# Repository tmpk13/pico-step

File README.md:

# pico-step

Closed-loop stepper driver board: RP2354A + TMC5241 motion controller and
driver (integrated 65 V bridges) + TLE5012B magnetic angle sensor.
USB-C powered logic, separate motor supply (VM) up to 48 V.

The schematic is drawn as text in `tsch/` for the text-schematic tool
`tsch` (set `TSCH` to its binary when it is not on the PATH); `mise run sch`
builds it into `pico-step.kicad_sch`, which is generated and not committed.

```sh
mise run install   # test deps
mise run sch-check # check the tsch/ drawing (fast, no KiCad)
mise run sch       # tsch/ -> pico-step.kicad_sch + sheets, proven with kicad-cli
mise run erc
mise run test
mise run render    # build/tsch/pico-step-<sheet>.png
mise run pcb-sync  # board <- schematic (footprints, values, nets), keeps placement
mise run pcb-place # placement table -> board (overwrites GUI moves)
mise run pcb-dsn   # build/pico-step.dsn for freerouting
mise run pcb-autoroute # FREEROUTING=<launcher or jar> freerouting -> build/pico-step.ses
mise run pcb-ses   # import the session and refill zones
mise run pcb-gnd   # GND stitching vias after routing
mise run pcb-drc
mise run pcb-render # build/pcb-top.png, build/pcb-bottom.png
```

The PCB is a 42 mm NEMA17 back-mount, 2 layers, 0.15 mm rules; the floor
plan is in `notes/pcb.md`.

See `ARCHITECTURE.md` for the block diagram, `BOM.md` for sourced parts,
`PARTS_BY_CHIP.md` for which parts support which chip,
`DIGIKEY.md` for the order list,
`TODO.md` for open work.

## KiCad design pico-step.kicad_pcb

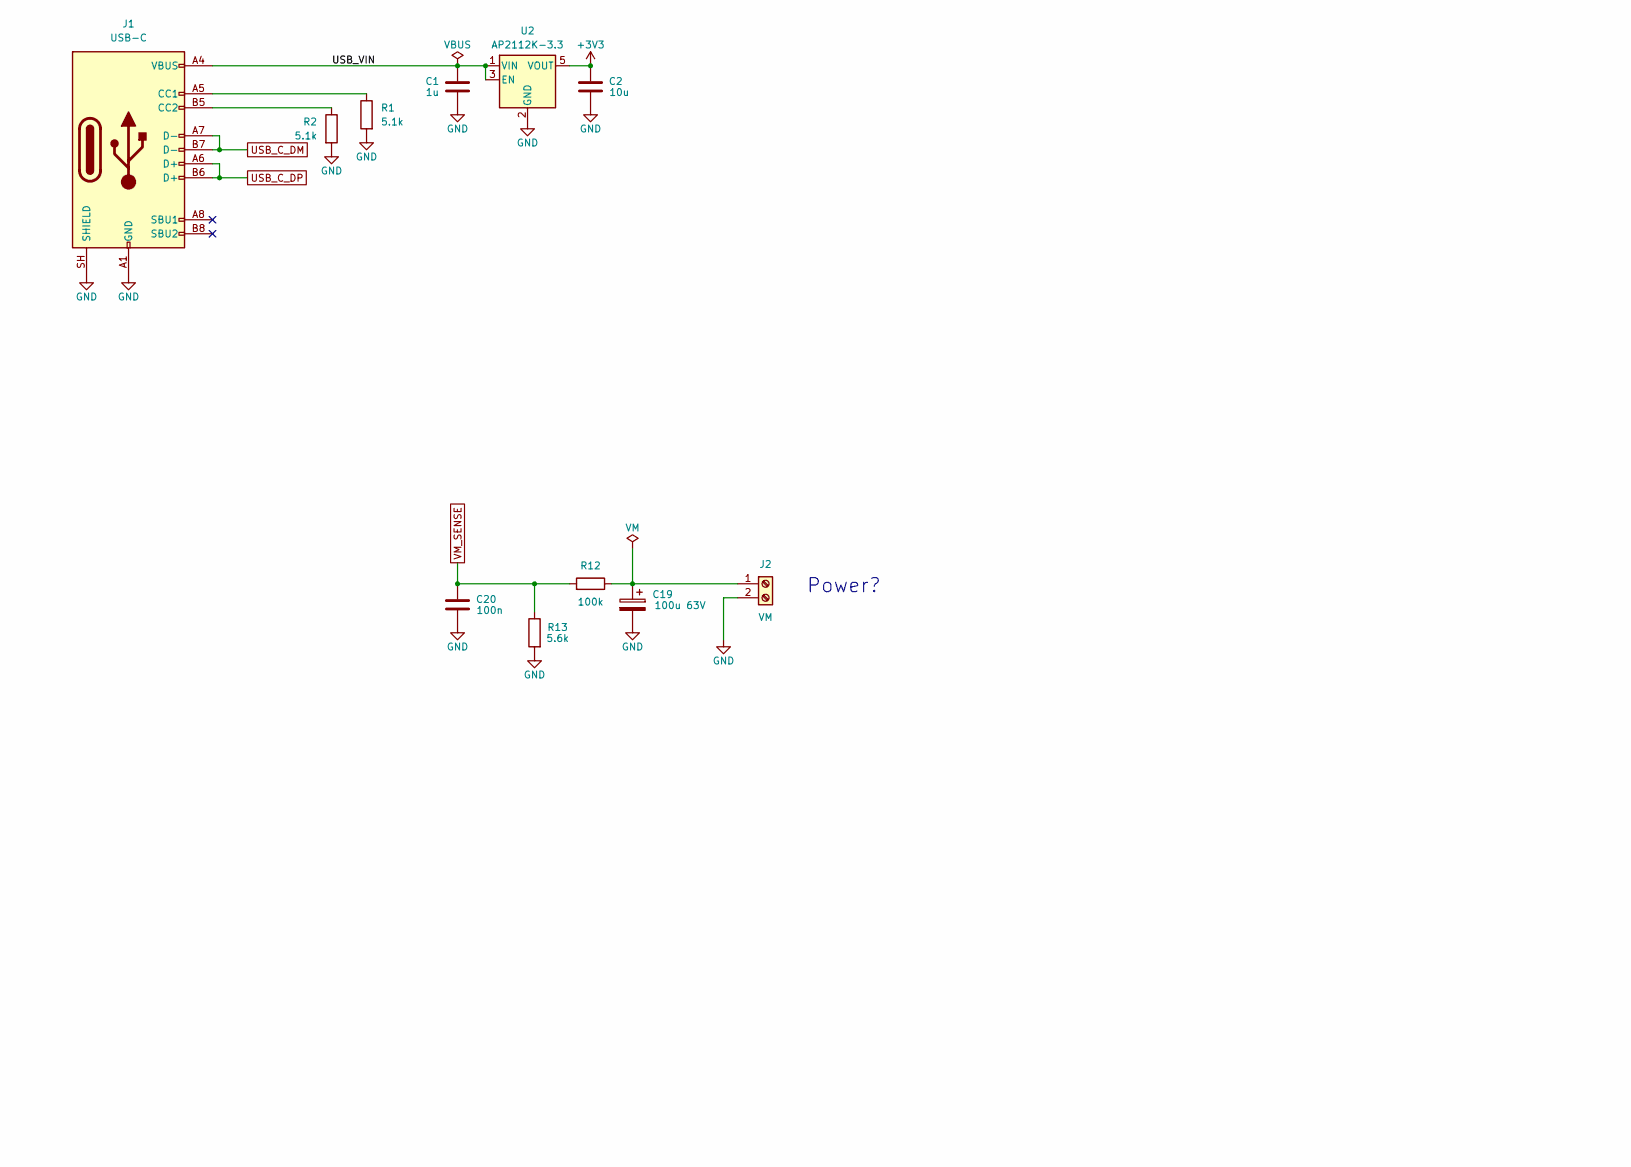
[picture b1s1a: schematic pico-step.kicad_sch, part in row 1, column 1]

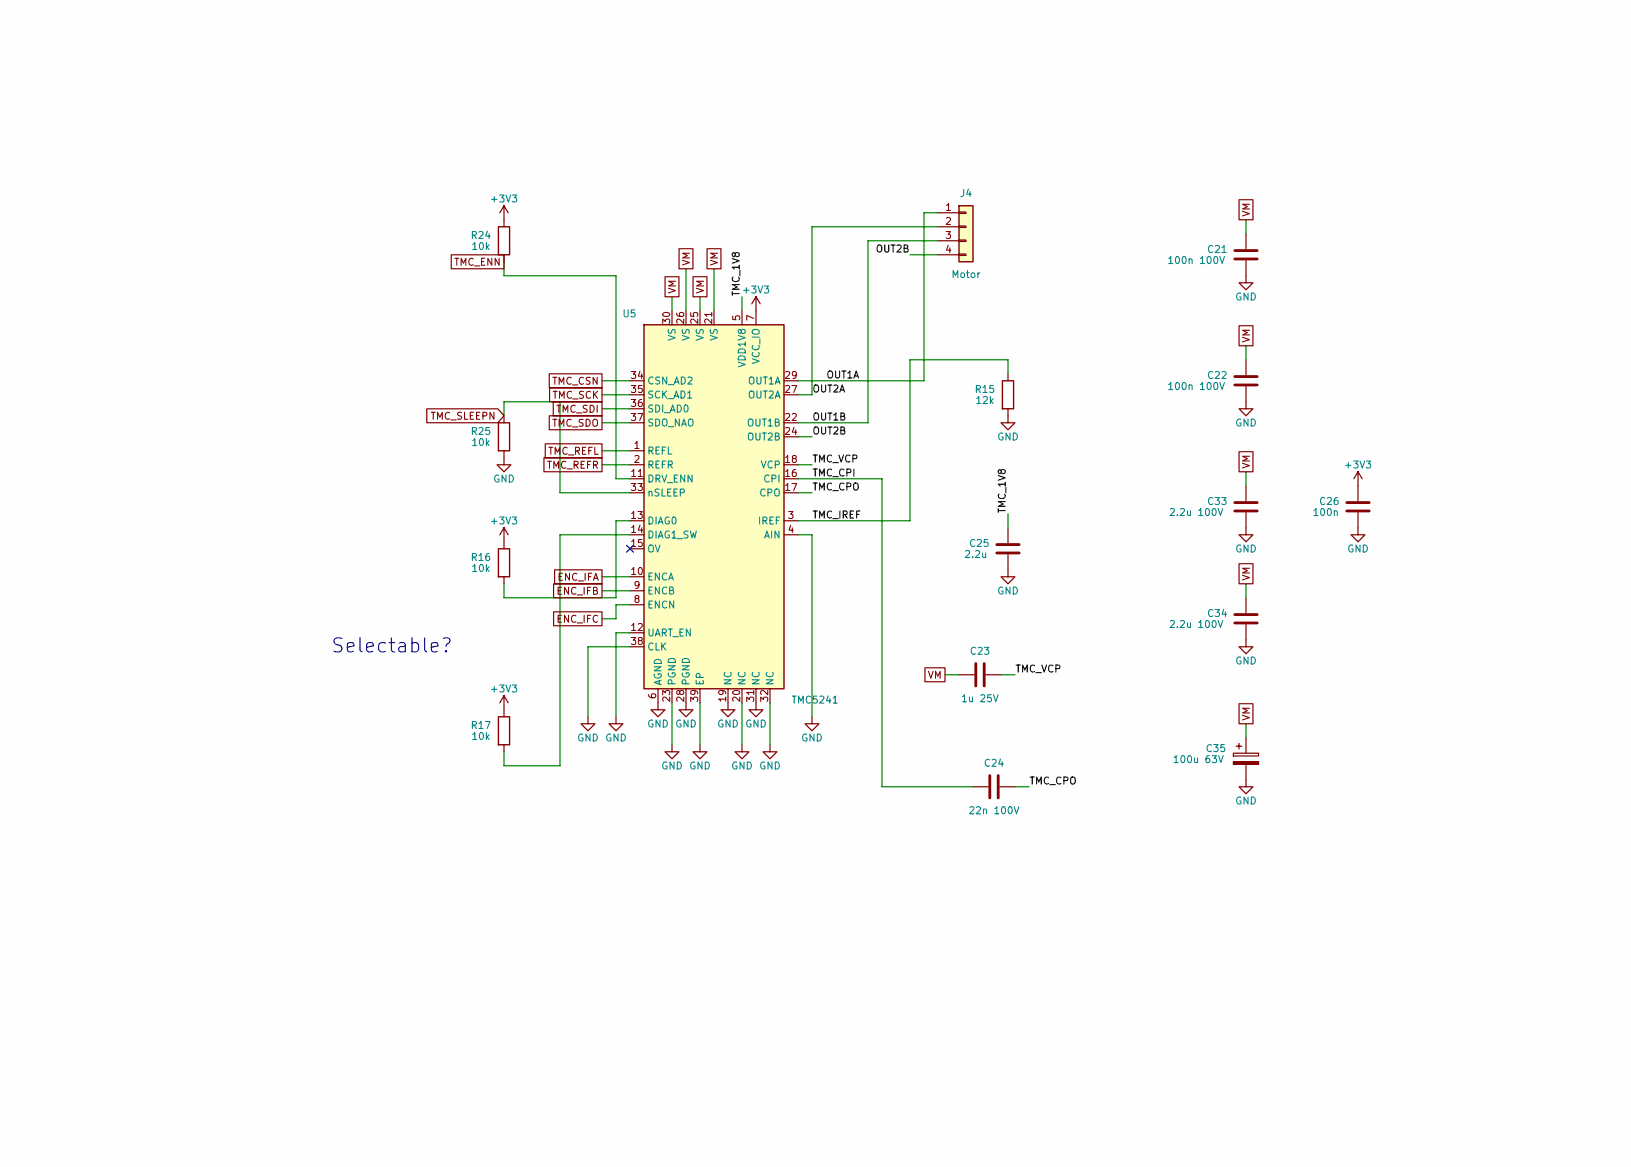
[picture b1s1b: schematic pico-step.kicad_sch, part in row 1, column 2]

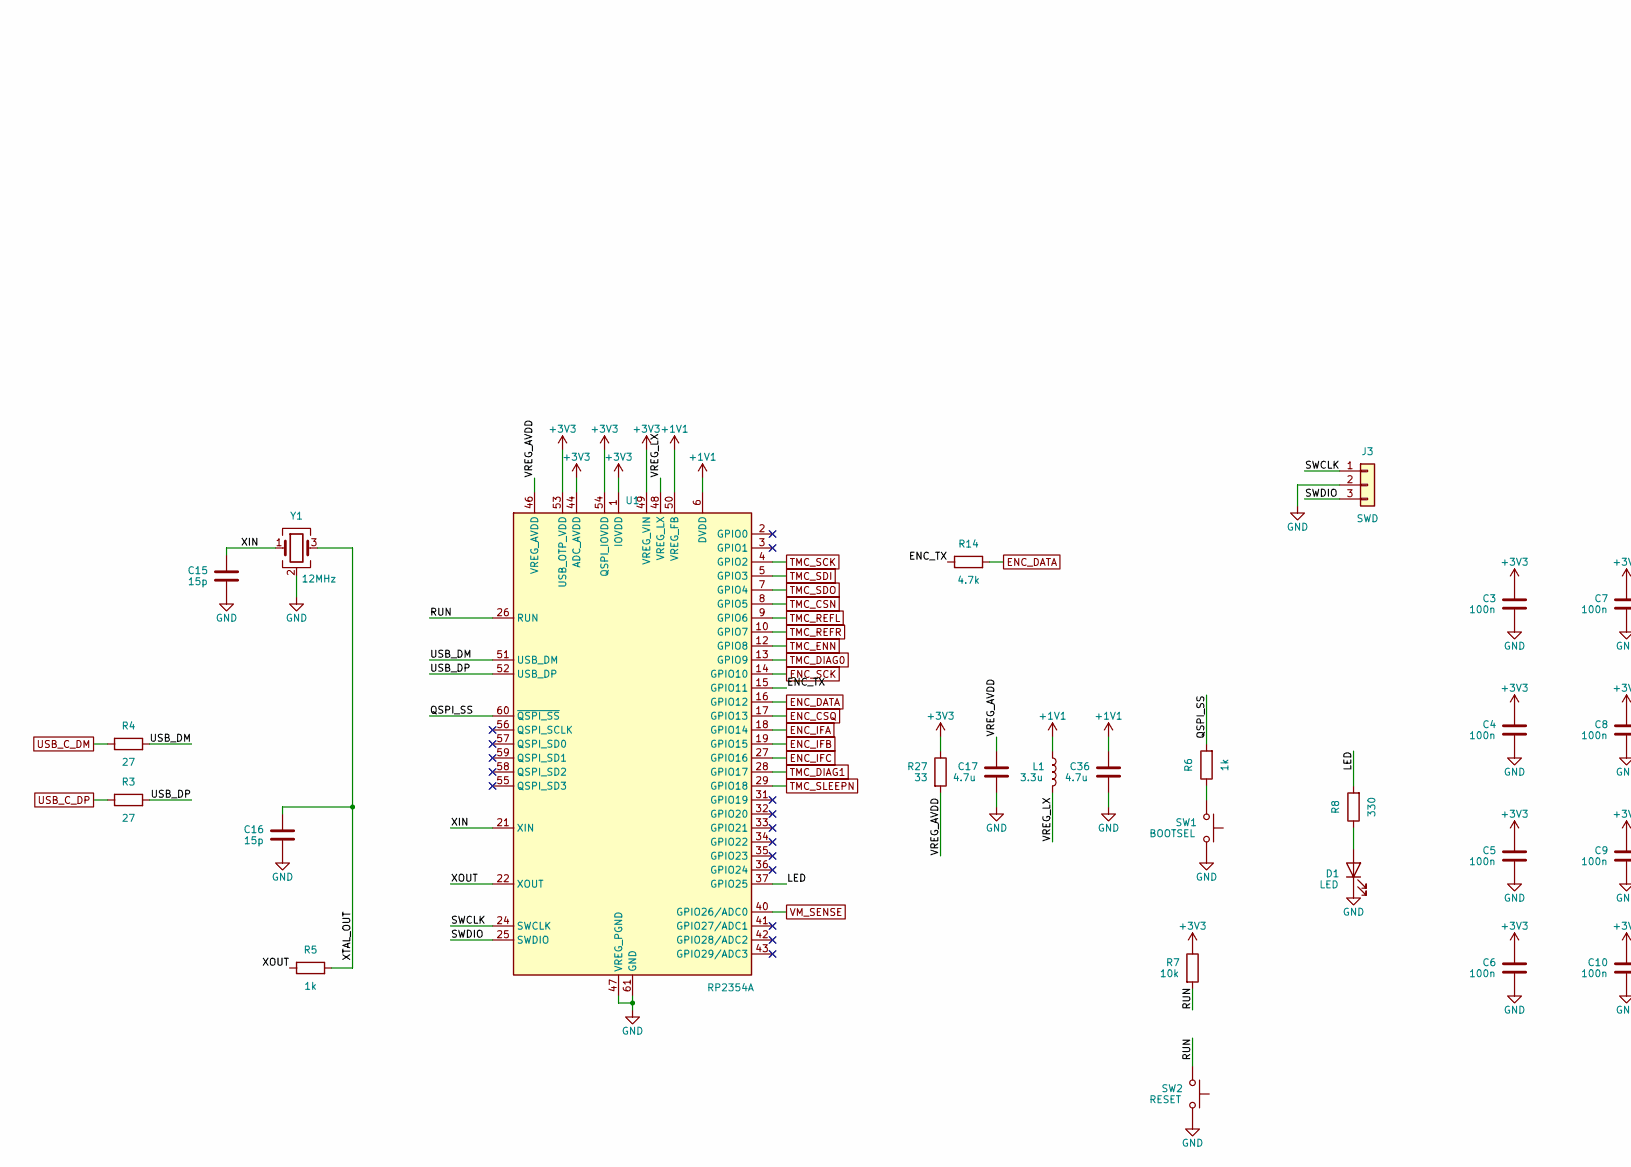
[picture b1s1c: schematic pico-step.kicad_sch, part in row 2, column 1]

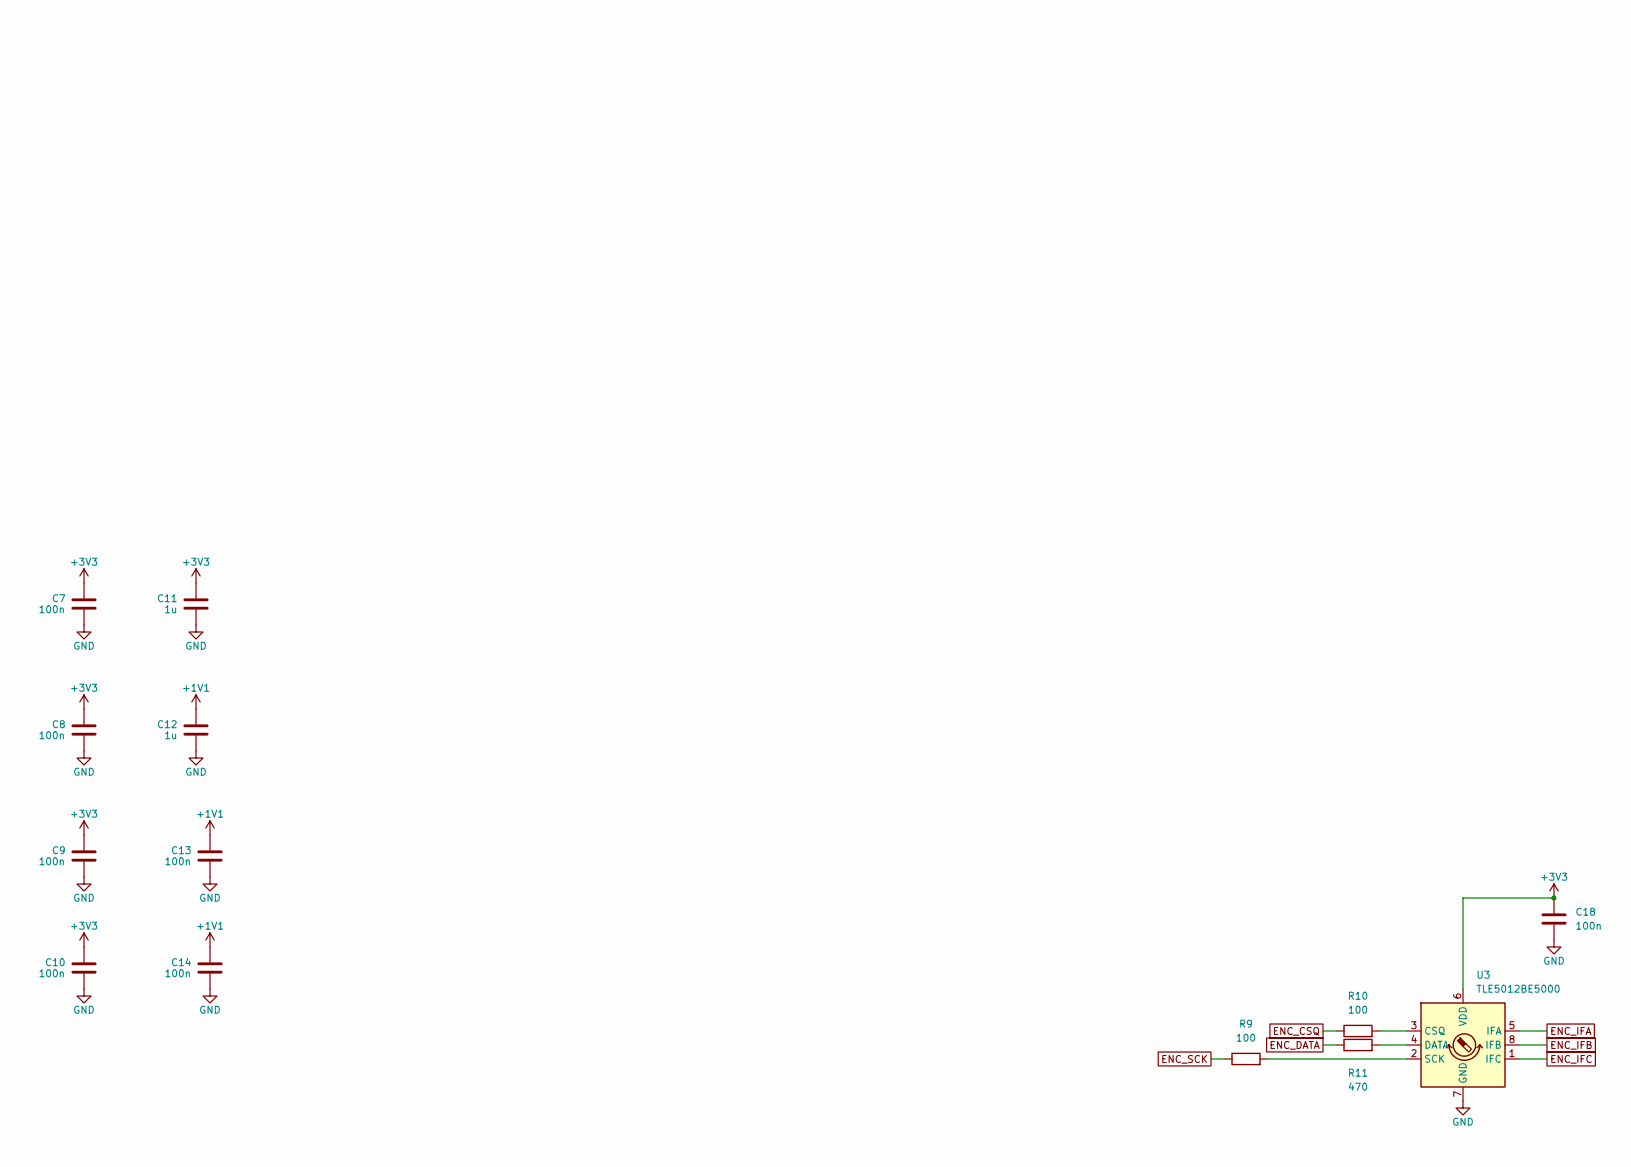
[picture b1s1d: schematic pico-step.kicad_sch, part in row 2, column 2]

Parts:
C1, C11, C12: 1u; C_0603_1608Metric
C2: 10u; C_0805_2012Metric
C3, C4, C5, C6, C7, C8, C9, C10, C13, C14, C18, C20, C26: 100n; C_0603_1608Metric
C15, C16: 15p; C_0603_1608Metric
C17, C36: 4.7u; C_0603_1608Metric
C19, C35: 100u 63V; CP_Elec_10x10.5
C21, C22: 100n 100V; C_0603_1608Metric
C23: 1u 25V; C_0603_1608Metric
C24: 22n 100V; C_0603_1608Metric
C25: 2.2u; C_0603_1608Metric
C33, C34: 2.2u 100V; C_1210_3225Metric
D1: LED; LED_0603_1608Metric
J1: USB-C; USB_C_Receptacle_GCT_USB4105-xx-A_16P_SH; MPN USB4105-GF-A
J2: VM; TerminalBlock_Phoenix_MKDS-1,5-2-5.08_1x02_P5.08mm_Horizont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
J3: SWD; PinHeader_1x03_P2.54mm_Vertical
J4: Motor; JST_XH_B4B-XH-A_1x04_P2.50mm_Vertical
L1: 3.3u; L_Abracon_AOTA-B201610; MPN AOTA-B201610S3R3-101-T
R1, R2: 5.1k; R_0603_1608Metric
R3, R4: 27; R_0603_1608Metric
R5, R6: 1k; R_0603_1608Metric
R7, R16, R17, R24, R25: 10k; R_0603_1608Metric
R8: 330; R_0603_1608Metric
R9, R10: 100; R_0603_1608Metric
R11: 470; R_0603_1608Metric
R12: 100k; R_0603_1608Metric
R13: 5.6k; R_0603_1608Metric
R14: 4.7k; R_0603_1608Metric
R15: 12k; R_0603_1608Metric
R27: 33; R_0603_1608Metric
SW1: BOOTSEL; SW_SPST_PTS810
SW2: RESET; SW_SPST_PTS810
U1: RP2354A; QFN-60-1EP_7x7mm_P0.4mm_EP3.4x3.4mm; MPN SC1511-A4
U2: AP2112K-3.3; SOT-23-5; MPN AP2112K-3.3TRG1
U3: TLE5012BE5000; Infineon_PG-DSO-8; MPN TLE5012BE5000XUMA1
U5: TMC5241; ADI_TQFN-38-1EP_5x7mm_P0.5mm_EP3.65x5.6mm_ThermalVias; MPN TMC5241ATU+T
Y1: 12MHz; Crystal_SMD_3225-4Pin_3.2x2.5mm; MPN ABM8-272-T3

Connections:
+1V1: C12.1, C13.1, C14.1, C36.1, L1.1, U1.6 (DVDD), U1.23 (DVDD), U1.39 (DVDD), U1.50 (VREG_FB)
+3V3: C2.1, C3.1, C4.1, C5.1, C6.1, C7.1, C8.1, C9.1, C10.1, C11.1, C18.1, C26.1, R7.1, R16.1, R17.1, R24.1, R27.1, U1.1 (IOVDD), U1.11 (IOVDD), U1.20 (IOVDD), U1.30 (IOVDD), U1.38 (IOVDD), U1.44 (ADC_AVDD), U1.45 (IOVDD), U1.49 (VREG_VIN), U1.53 (USB_OTP_VDD), U1.54 (QSPI_IOVDD), U2.5 (VOUT), U3.6 (VDD), U5.7 (VCC_IO)
/driver/OUT1A: J4.1, U5.29 (OUT1A)
/driver/OUT1B: J4.3, U5.22 (OUT1B)
/driver/OUT2A: J4.2, U5.27 (OUT2A)
/driver/OUT2B: J4.4, U5.24 (OUT2B)
ENC_CSQ: R10.1, U1.17 (GPIO13)
ENC_DATA: R11.1, R14.2, U1.16 (GPIO12)
ENC_IFA: U1.18 (GPIO14), U3.5 (IFA), U5.10 (ENCA)
ENC_IFB: U1.19 (GPIO15), U3.8 (IFB), U5.9 (ENCB)
ENC_IFC: U1.27 (GPIO16), U3.1 (IFC), U5.8 (ENCN)
ENC_SCK: R9.1, U1.14 (GPIO10)
ENC_TX: R14.1, U1.15 (GPIO11)
GND: C1.2, C2.2, C3.2, C4.2, C5.2, C6.2, C7.2, C8.2, C9.2, C10.2, C11.2, C12.2, C13.2, C14.2, C15.2, C16.2, C17.2, C18.2, C19.2, C20.2, C21.2, C22.2, C25.2, C26.2, C33.2, C34.2, C35.2, C36.2, D1.1 (K), J1.A1 (GND), J1.A12 (GND), J1.B1 (GND), J1.B12 (GND), J1.SH (SHIELD), J2.2, J3.2, R1.2, R2.2, R13.2, R15.2, R25.2, SW1.2, SW2.2, U1.47 (VREG_PGND), U1.61 (GND), U2.2 (GND), U3.7 (GND), U5.4 (AIN), U5.6 (AGND), U5.12 (UART_EN), U5.19 (NC), U5.20 (NC), U5.23 (PGND), U5.28 (PGND), U5.31 (NC), U5.32 (NC), U5.38 (CLK), U5.39 (EP), Y1.2 (G), Y1.4 (G)
unnamed: C16.1, R5.2, Y1.3
unnamed: D1.2 (A), R8.1
unnamed: J1.A5 (CC1), R1.1
unnamed: J1.B5 (CC2), R2.1
unnamed: J1.A6 (D+), J1.B6 (D+), R3.1
unnamed: J1.A7 (D-), J1.B7 (D-), R4.1
unnamed: J3.1, U1.24 (SWCLK)
unnamed: J3.3, U1.25 (SWDIO)
unnamed: R6.1, SW1.1
unnamed: C17.1, R27.2, U1.46 (VREG_AVDD)
unnamed: L1.2, U1.48 (VREG_LX)
unnamed: R8.2, U1.37 (GPIO25)
unnamed: R6.2, U1.60 (~QSPI_SS)
unnamed: R7.2, SW2.1, U1.26 (RUN)
unnamed: C15.1, U1.21 (XIN), Y1.1
unnamed: R5.1, U1.22 (XOUT)
unnamed: C1.1, J1.A4 (VBUS), J1.A9 (VBUS), J1.B4 (VBUS), J1.B9 (VBUS), U2.1 (VIN), U2.3 (EN)
unnamed: R10.2, U3.3 (CSQ)
unnamed: R11.2, U3.4 (DATA)
unnamed: R9.2, U3.2 (SCK)
unnamed: C24.1, U5.16 (CPI)
unnamed: C24.2, U5.17 (CPO)
unnamed: R16.2, U5.13 (DIAG0)
unnamed: R17.2, U5.14 (DIAG1_SW)
unnamed: R15.1, U5.3 (IREF)
unnamed: C23.2, U5.18 (VCP)
unnamed: C25.1, U5.5 (VDD1V8)
TMC_CSN: U1.8 (GPIO5), U5.34 (CSN_AD2)
TMC_DIAG0: U1.13 (GPIO9)
TMC_DIAG1: U1.28 (GPIO17)
TMC_ENN: R24.2, U1.12 (GPIO8), U5.11 (DRV_ENN)
TMC_REFL: U1.9 (GPIO6), U5.1 (REFL)
TMC_REFR: U1.10 (GPIO7), U5.2 (REFR)
TMC_SCK: U1.4 (GPIO2), U5.35 (SCK_AD1)
TMC_SDI: U1.5 (GPIO3), U5.36 (SDI_AD0)
TMC_SDO: U1.7 (GPIO4), U5.37 (SDO_NAO)
TMC_SLEEPN: R25.1, U1.29 (GPIO18), U5.33 (nSLEEP)
USB_DM: R4.2, U1.51 (USB_DM)
USB_DP: R3.2, U1.52 (USB_DP)
VM: C21.1, C22.1, C23.1, C33.1, C34.1, C35.1, U5.21 (VS), U5.25 (VS), U5.26 (VS), U5.30 (VS)
VM_IN: C19.1, J2.1, R12.1
VM_SENSE: C20.1, R12.2, R13.1, U1.40 (GPIO26/ADC0)

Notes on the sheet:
Selectable?
Power?

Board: 4 copper layers, 63 parts (14 on the bottom side), 54 nets, no tracks yet.

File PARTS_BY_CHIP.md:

# Parts by chip

Every one of the 63 parts on the board, grouped by the chip it supports.

## U1 RP2354A

| Function | Parts |
| --- | --- |
| Decoupling, IOVDD | C3..C8 100n |
| Decoupling, USB_OTP_VDD + QSPI_IOVDD / ADC_AVDD | C9 100n, C10 100n |
| Core regulator, CIN / COUT / inductor | C11 4.7u, C12 4.7u, L1 3.3u |
| Core regulator, VREG_AVDD filter | R27 33, C17 4.7u |
| Decoupling, DVDD (pins 6, 39, 23) | C13 100n, C14 100n, C36 4.7u |
| 12 MHz crystal | Y1, C15 15p, C16 15p, R5 1k (XOUT) |
| USB series resistors | R3 27, R4 27 |
| BOOTSEL and reset | R6 1k, SW1 BOOTSEL, R7 10k, SW2 RESET |
| SWD header | J3 |
| Status LED (GPIO25) | R8 330, D1 |

## U5 TMC5241

| Function | Parts |
| --- | --- |
| VS decoupling, pin 30 end / pin 21 end of the VS/OUT row | C21 100n 100V, C33 2.2u 100V / C22 100n 100V, C34 2.2u 100V |
| VS bulk | C35 100u 63V |
| Charge pump | C23 1u 25V (VCP-VS), C24 22n 100V (CPI-CPO) |
| VDD1V8 regulator | C25 2.2u |
| VCC_IO | C26 100n |
| Full-scale current (RREF) | R15 12k |
| DIAG0/DIAG1 pull-ups | R16 10k, R17 10k |
| DRV_ENN pull-up (off during MCU reset) | R24 10k |
| nSLEEP pull-down (asleep until firmware wakes it) | R25 10k |
| Motor connector | J4 |

## U3 TLE5012B

| Function | Parts |
| --- | --- |
| Decoupling | C18 100n |
| SSC series resistors | R9 100 (SCK), R10 100 (CSQ), R11 470 (DATA) |
| SPI1 TX into DATA (TX cannot tri-state) | R14 4.7k |

## U2 AP2112K-3.3

| Function | Parts |
| --- | --- |
| Input / output caps | C1 1u, C2 10u |

## Not tied to one chip

| Function | Parts |
| --- | --- |
| USB-C input, CC pull-downs | J1, R1 5.1k, R2 5.1k |
| Motor supply terminal and bulk (feeds U5) | J2, C19 100u 63V |
| VM_SENSE divider (feeds U1 GPIO26 ADC0) | R12 100k, R13 5.6k, C20 100n |

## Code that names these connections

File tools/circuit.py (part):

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connect("GND", "J3.2")
connect("SWDIO", "U1.25", "J3.3")

# Status LED on GPIO25
res("R8", "330")
part("D1", "Device:LED", "LED", "LED_SMD:LED_0603_1608Metric")
connect("LED", "U1.37", "R8.1")
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res("R14", "4.7k")
connect("+3V3", "U3.6", "C18.1")
connect("GND", "U3.7", "C18.2")
connect("ENC_SCK", "U1.14", "R9.1")       # GPIO10 SPI1 SCK
connect("ENC_SCK_S", "R9.2", "U3.2")
connect("ENC_CSQ", "U1.17", "R10.1")      # GPIO13 SPI1 CSn
connect("ENC_CSQ_S", "R10.2", "U3.3")
connect("ENC_TX", "U1.15", "R14.1")       # GPIO11 SPI1 TX
connect("ENC_DATA", "U1.16", "R14.2", "R11.1")  # GPIO12 SPI1 RX
connect("ENC_DATA_S", "R11.2", "U3.4")
connect("ENC_IFA", "U1.18", "U3.5")       # GPIO14, PWM output in E5000
connect("ENC_IFB", "U1.19", "U3.8")       # GPIO15
connect("ENC_IFC", "U1.27", "U3.1")       # GPIO16

groups.append({"name": "encoder", "stages": [
    ["R9", "R10", "R14", "R11"], ["U3", "C18"],
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cap("C20", "100n")
connect("VM", "J2.1", "C19.1", "R12.1")
connect("GND", "J2.2", "C19.2", "R13.2", "C20.2")
connect("VM_SENSE", "R12.2", "R13.1", "C20.1", "U1.40")  # GPIO26 ADC0

groups.append({"name": "motor_supply", "stages": [["J2"], ["C19"], ["R12", "R13", "C20"]]})

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connect("OUT1B", "U5.22", "J4.3")
connect("OUT2B", "U5.24", "J4.4")

# MCU interface: SPI0 on GPIO2..5.
connect("TMC_SCK", "U1.4", "U5.35")     # GPIO2 SPI0 SCK
connect("TMC_SDI", "U1.5", "U5.36")     # GPIO3 SPI0 TX
connect("TMC_SDO", "U1.7", "U5.37")     # GPIO4 SPI0 RX
connect("TMC_CSN", "U1.8", "U5.34")     # GPIO5 SPI0 CSn
# Reference switch inputs of the ramp generator, driven by the MCU (no
# STEP/DIR input on this part).
connect("TMC_REFL", "U1.9", "U5.1")     # GPIO6
connect("TMC_REFR", "U1.10", "U5.2")    # GPIO7
# DRV_ENN has an internal ~100k pull-up, which loses to the MCU's ~50k reset
# pull-down. 10k to 3V3 holds 2.75 V (VIH 0.7 x VCC_IO = 2.31 V): outputs
# stay off until firmware drives GPIO8 low.
connect("TMC_ENN", "U1.12", "U5.11", "R24.2")    # GPIO8
connect("TMC_DIAG0", "U1.13", "U5.13", "R16.2")  # GPIO9
connect("TMC_DIAG1", "U1.28", "U5.14", "R17.2")  # GPIO17
# nSLEEP low is sleep with every register cleared; a >30 us low pulse is a
# reset. The 10k pull-down keeps the driver asleep (bridges off, VS draw
# under 25 uA) until firmware raises GPIO18. The pin is VS rated with a
# 0.9 V input threshold, so 3.3 V drives it.
connect("TMC_SLEEPN", "U1.29", "U5.33", "R25.1")  # GPIO18
# The angle sensor's IIF outputs feed the encoder inputs, so firmware can
# switch the TLE5012B to IIF and let the TMC5241 count.
connect("ENC_IFA", "U5.10")
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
